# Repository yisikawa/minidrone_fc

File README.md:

# minidrone_fc — ミニドローン制御基板 KiCadプロジェクト

1S LiPo / 8520コアレスモーター×4 / 目標58g・上限70g

回路図は生成済みです。手で描く必要はありません。

---

## 1. 使い方

1. このフォルダごと `D:\KicadProjects\` などに置く（`D:\Kicad`
   の中には置かないでください。KiCad更新時に消える可能性があります）
2. `minidrone_fc.kicad_pro` をダブルクリック
3. 回路図（`.kicad_sch`）を開く

**KiCad 10で開くとファイル形式の変換確認が出ます。**
このプロジェクトはKiCad 7形式で生成されているためです。
「はい」で変換してください。以後は10形式で保存されます。

---

## 2. 最初にやること: XIAOのフットプリント設定

**U1のフットプリントは意図的に空欄にしてあります。**
XIAOはKiCad公式ライブラリに含まれず、環境によってライブラリ名が
変わるため、こちらで決め打ちできませんでした。

手順:

1. https://github.com/Seeed-Studio/OPL_Kicad_Library をZIPで取得
2. 展開し、`Seeed Studio XIAO Series Library/` 内の `.kicad_sym` を
   設定 → シンボルライブラリを管理 から追加
3. フットプリントは `.pretty` フォルダに入っていないと認識されません。
   単体の `.kicad_mod` ファイルの場合は `Seeed_XIAO.pretty` という
   フォルダを作って中に移動してから、
   設定 → フットプリントライブラリを管理 で追加
4. 回路図でU1を選択 → E キー → Footprintフィールドに
   `Seeed_XIAO:XIAO-ESP32C3-SMD` のような実際の名前を入力

U1のシンボル自体はこのプロジェクト内の `minidrone.kicad_sym` に
同梱してあるので、シンボルライブラリの導入は必須ではありません。
必要なのはフットプリントだけです。

---

## 3. 検証済みの内容

このプロジェクトは生成後、KiCadのエンジン（kicad-cli）で
以下を実機検証しています。

| 検証項目 | 結果 |
|---|---|
| 回路図ファイルの読み込み | 成功 |
| 基板ファイルの読み込み | 成功 |
| 部品点数 | 37点（設計意図と一致） |
| フットプリント割り当て | 全点一致（U1除く） |
| ネット数 | 22ネット |
| 接続点の総数 | 96点 |
| ネットリスト照合 | **全ネット完全一致** |
| 意図しない結線 | なし |
| 未結線ピン | 16点（すべてno_connect指定済み） |

つまり、書き出したネットリストが設計表と1本残らず一致することを
確認済みです。回路図の入力ミスはありません。

---

## 4. 設計資料からの変更点

基板化の過程で判明した誤りを訂正しています。

| 項目 | 変更前 | 変更後 | 理由 |
|---|---|---|---|
| 極性コンデンサ | `Device:CP` | `Device:C_Polarized` | CPはKiCad 5時代の名前。現行ライブラリに存在しない |
| フライバックダイオード | SS14 | **SS24** | SS14は1A定格。モーター電流1.62Aに対し余裕が乏しい。SS24は2A定格で、フットプリントは同じD_SMAなのでレイアウト変更不要 |
| C3〜C6の接続先 | Qのドレイン–ソース間 | **VBAT–GND間** | 高周波電流ループを閉じるのは電源側。低側スイッチではこちらが標準 |
| PTCヒューズ・電源SW | あり | **削除** | 6.5Aでは直列抵抗による電圧降下が推力損失に直結する |

---

## 5. ピン割り当て（ESP32-C3の制約を反映済み）

| XIAOピン | GPIO | ネット | 備考 |
|---|---|---|---|
| D0 | GPIO2 | 未使用 | ストラッピングピン。使用不可 |
| D1 | GPIO3 | BATT_SENSE | ADC1。Wi-Fi動作中も使える |
| D2 | GPIO4 | GATE_FL | |
| D3 | GPIO5 | GATE_FR | |
| D4 | GPIO6 | SDA | |
| D5 | GPIO7 | SCL | |
| D6 | GPIO21 | GATE_RL | |
| D7 | GPIO20 | IMU_INT | MPU6050のデータレディ割り込み |
| D8 | GPIO8 | 未使用 | ストラッピングピン |
| D9 | GPIO9 | 未使用 | BOOTピン |
| D10 | GPIO10 | GATE_RR | |

**A0はD0と同一ピンです。** そしてGPIO2はストラッピングピンなので、
電圧センスはD1（GPIO3）に置いてあります。またESP32-C3のADC2は
Wi-Fi動作中に使えないため、ADC1に属するピンでなければなりません。

D7をIMU割り込みに使っているので、将来UART受信機を追加する場合は
再割り当てが必要です。

---

## 6. 次の手順（基板レイアウト）

1. Eeschemaで ツール → フットプリントを割り当て を開き、U1だけ設定
2. 検査 → エレクトリカルルールチェック(ERC) を実行
3. ツール → 基板エディタで基板を更新
4. 基板の外形（Edge.Cuts）を35×35mmで描く
5. 配置は以下の順序で。**この順序が重要です**
   - モーターパッド J2〜J5 を四隅に
   - Q1〜Q4 と D1〜D4 を対応するパッドの直近（5mm以内）に
   - C3〜C6 を各Qの直近に
   - U1を中央、USB-Cが基板端から出る向きに
   - U2を裏面中央、モーター電流経路を避けた位置に
6. デザインルール: 最小クリアランス0.2mm、最小トレース幅0.25mm、
   ビア0.6mm/ドリル0.3mm
7. VBATとGNDはトレースではなく**ベタ（カッパープアー）**で。
   6.5Aには1oz銅で約4.0mm幅のトレースが必要で、35mm角では引けません
8. M_FL〜M_RRは1.0mm幅以上

### レイアウトで最も重要な点

**フライバックループの面積を最小化してください。**
モーターOFFの瞬間、逆起電力が モーター → D → VBAT → モーター を
流れます。このループが囲む面積がそのままノイズの放射源になり、
MPU6050の読み値を汚します。D1〜D4は必ずモーターパッドの真横に、
ビアを挟まずに配置してください。

---

## 7. 未検証事項

- **XIAOフットプリントの実寸**: Seeedのライブラリで裏面パッドや
  サーマルパッドの欠落が報告されています。実物を基板に当てて
  確認してください
- **MPU6050のQFN-24実装**: 手はんだは難度が高めです。困難なら
  GY-521完成基板（+1〜2g）に戻す判断もあり得ます
- **フレーム側の穴位置**: モーターパッドの座標はフレーム設計と
  同時に決める必要があります。基板レイアウトの前にフレーム寸法を
  確定させてください
- **ガーバー出力は未実施**: 発注前にDRCとガーバービューアでの
  目視確認を必ず行ってください

---

## 8. rev2 での修正（ERC結果を反映）

初版に対してERCを実行した結果、エラー3件・警告137件を修正しました。

| 症状 | 件数 | 原因 | 対応 |
|---|---|---|---|
| `power_pin_not_driven` | 3（エラー） | XIAOの3V3ピンを`power_in`と定義していた。実際はレギュレータ**出力**。またGND/VMCUに駆動源が明示されていなかった | 3V3を`power_out`に修正。VBAT/GND/VMCUにPWR_FLAGを追加 |
| `endpoint_off_grid` | 133（警告） | 部品座標が1.27mm（50mil）グリッドに乗っていなかった | 全部品を1.27mmグリッドにスナップ |
| `lib_symbol_mismatch` | 4（警告） | AO3400Aは本来`extends BSS138`の派生シンボル。展開して埋め込んだためライブラリ本体と差異が出る | 下記参照 |

### lib_symbol_mismatch について

これは**動作に影響しない表示上の警告**です。KiCad 7の回路図フォーマットが
`extends` を受け付けないため、生成側で展開する必要がありました。

解消したい場合は、KiCad 10で
**ツール → シンボルをライブラリから更新** を実行してください。
埋め込みコピーがKiCad 10のライブラリ版に置き換わり、警告が消えます。
接続には影響しません。

### 修正後の検証結果

- 回路図・基板ファイルの読み込み: 成功
- ネットリスト照合: **全22ネット・96接続点が完全一致**
- ワイヤ端点198点・ラベル99点・no_connect16点: **すべてグリッド上（off-grid 0）**
- BOM部品数: 37点（PWR_FLAG 3点はBOM除外）

---

## 9. rev2.1 での変更（2026-09-19）: 昇降圧DC-DC追加 + 4層化

### 9.1 なぜ必要だったか — 電源の設計欠陥

改訂前の電源経路は次のとおりでした。

```
VBAT (3.0-4.2V) --[D5 SS24, 約0.4V drop]--> VMCU --> U1(XIAO) pin14 "5V"
                        XIAO内蔵LDO --> +3V3 --> U2 GY-521, U3 BMP280
```

**この基板には昇圧素子が1つもありません。** そのため電池電圧が
「3.3V + LDOドロップアウト」を下回れば、3V3 レールは必ず追従して下がります。

8520コアレスモーター4個で 6.5A を引くと電池は 3.7V→3.4V 程度に沈み、
そこから D5 の 0.4V を引いて VMCU ≈ 3.0V、さらに XIAO 内蔵 LDO の
ドロップアウトを引くと **3V3 は 2.8〜2.95V**。
ESP32-C3 の動作下限 3.0V を公称電圧ですら下回っており、
**スロットルを上げた瞬間に MCU がリセットする**状態でした。

D5 が 0.4V を捨てていたのが最大の要因です。

### 9.2 対策 — TPS63002 昇降圧DC-DC の挿入

```
VBAT --> U4 TPS63002 (昇降圧, 5V固定) --> [D5 SS24] --> VMCU --> XIAO 5Vピン
             |                                              XIAO内蔵LDO --> +3V3（変更なし）
             +-- L1 2.2uH, C10 10uF(in), C11 22uF(out), C12 0.1uF(VINA)
```

- 電池が 3.0V まで落ちても出力5V固定。D5 で 0.4V 落ちても **4.6V** が XIAO に入る。
  内蔵LDO が 3.3V を作るのに必要なのは 3.5V 程度なので**余裕1V以上**
- 3.3V を XIAO の 3V3 ピンに逆流注入せず、XIAO が本来想定する "5V" ピンから
  入れているので、内蔵LDO と競合しない
- **+3V3 ネット（GY-521・BMP280）は一切変更していません**
- D5 は流用。向きも不変で、上流が VBAT から V5V に変わっただけ
- 効率は昇圧90%×LDO66%＝約60%だが、MCU消費0.33Wに対しモーターが24Wなので
  損失増は全体の0.75%

### 9.3 4層化

| 層 | 内容 |
|---|---|
| L1 F.Cu | 信号 + U1/U2 + 既存の VBAT ベタ4枚（そのまま残置） |
| **L2 In1.Cu** | **ベタGND 全面 2949mm²** |
| **L3 In2.Cu** | **VBAT プレーン 全面 2811mm²** |
| L4 B.Cu | 信号 + SMD部品 + GNDベタ |

改訂前は 6.5A を 0.6mm トレースで流していました。内層プレーン全面に変更。
GND スティッチングビアを 133本、衝突判定付きで自動配置しています。

### 9.4 U4 のローカルクリアランス 0.1mm について

VSON-10 は 0.5mm ピッチ・パッド幅 0.28mm でパッド間が 0.22mm しかなく、
VBAT が属する Power ネットクラスの 0.25mm 要求を物理的に満たせません。
Power の 0.25mm はモーター大電流の配線・ベタ向けポリシーであり、
ファインピッチ IC のピン間に適用する意図ではないため、
U4 のフットプリントにローカル上書きを設定しています。
JLCPCB の製造限界は 0.1mm なので 0.22mm は十分製造可能です。

### 9.5 検証結果

| 項目 | 改訂前 | 改訂後 |
|---|---|---|
| DRC エラー | 0 | **0** |
| DRC 警告 | 32 | 37（増分5はすべてシルク重なり） |
| 未配線アイテム | 4 | **1**（改善） |
| schematic_parity | 0 | **0**（回路図と基板が完全一致） |
| ERC | warning 5 / error 0 | warning 5 / error 0（同一） |
| 既存部品のパッド-ネット変更 | — | **D5 pad2 の VBAT→V5V のみ** |

検証は `kicad-cli pcb drc` / `kicad-cli sch erc` で実施しています。
**KiCad MCP の `run_drc` は未接続アイテムを検査しないため、
発注前の最終確認は必ず `kicad-cli` か GUI の DRC で行ってください。**

### 9.6 まだ残っている課題

- **未配線1件**: GND ベタの孤立島が1つ残っています（改訂前は4件）。
  電気的な害はありませんが、気になる場合は GUI で該当箇所を確認してください
- **シルク警告 29+3件**: 新規部品 C10/C11/C12 のリファレンス文字が
  隣接銅箔に重なります。この一角は部品とビアで埋まっており逃がす余地が
  ありませんでした。JLCPCB はパッド上のシルクを自動クリップします
- **Gerber / BOM / 実装座標は再出力していません。** 4層基板として
  出力し直す必要があります
- **実機でのブラウンアウト解消は未検証です**

### 9.7 改訂前の状態に戻すには

改訂前 (rev2) の状態は最初のコミットにそのまま記録してあります。
タグ `rev2` / `rev2.1` から参照できます。

```
git show rev2 --stat      改訂前の内容
git diff rev2 rev2.1      今回の改訂差分
```

git 導入前に使っていた手動チェックポイント (`*.before-gy521`, `*.before-4layer` など)
とローカルのフルバックアップは、履歴で代替できるため追跡対象外にしています
(`.gitignore` 参照)。

詳細な作業記録は `docs/superpowers/plans/2026-09-19-buckboost-and-4layer.md`。

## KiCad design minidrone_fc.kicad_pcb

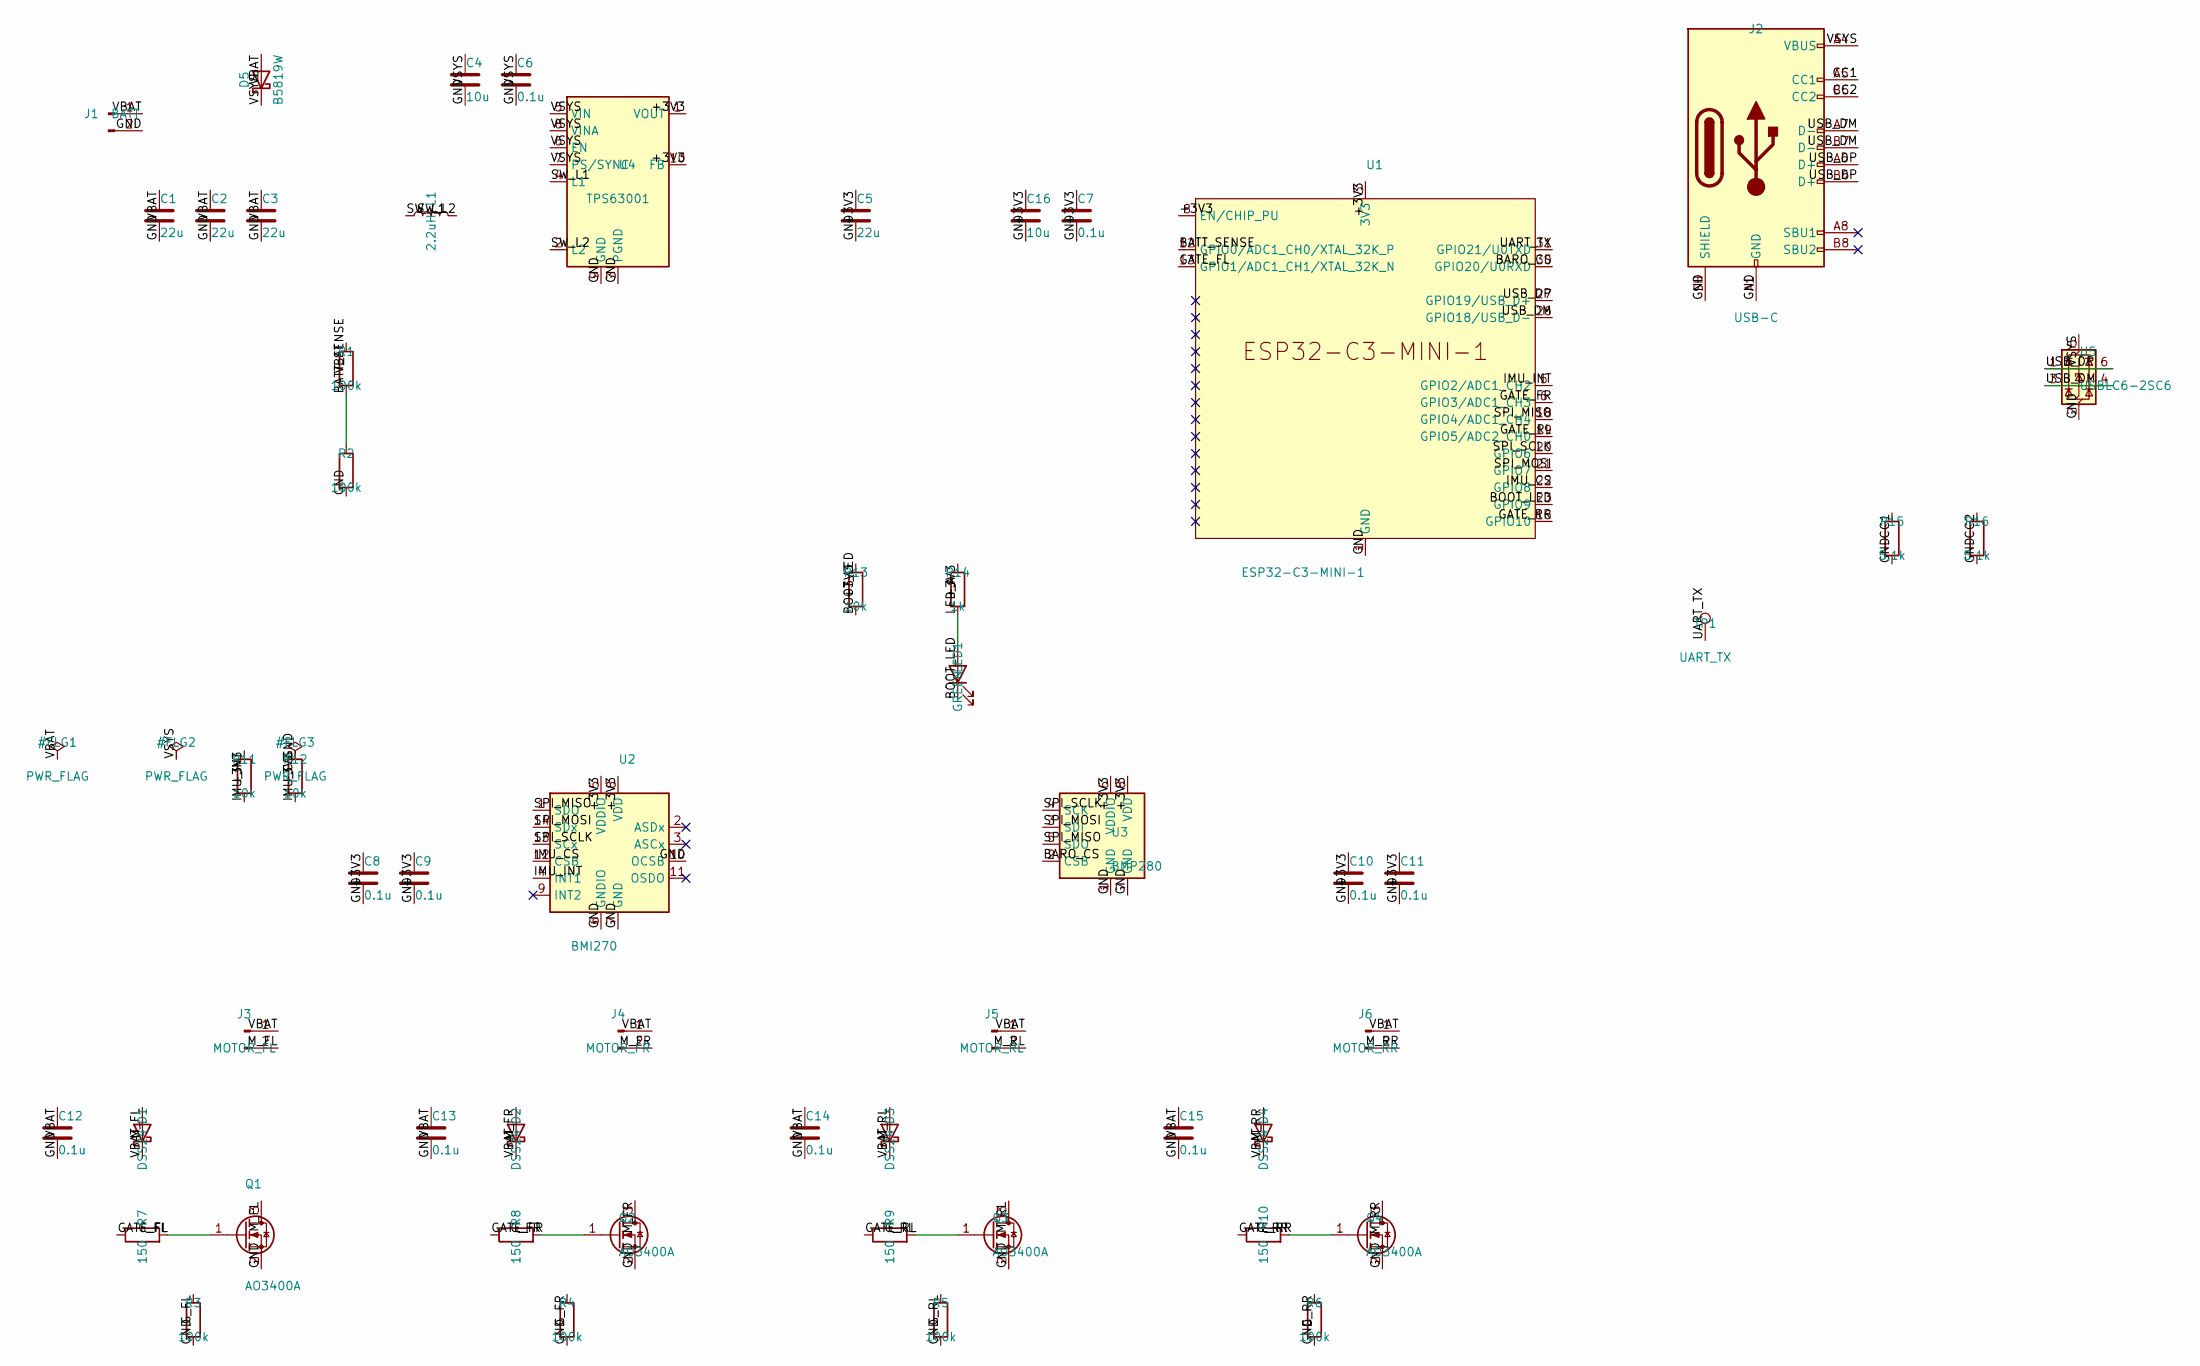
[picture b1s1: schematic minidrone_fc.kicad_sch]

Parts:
C1, C2, C3, C5: 22u; C_0805_2012Metric; LCSC C128856
C4, C16: 10u; C_0805_2012Metric; LCSC C15850
C6, C7, C8, C9, C10, C11, C12, C13, C14, C15: 0.1u; C_0603_1608Metric; LCSC C14663
D1, D2, D3, D4: DSS24; D_SOD-123F; MPN DSS24; LCSC C2923950
D5: B5819W; D_SOD-123; MPN B5819W; LCSC C2943878
J1: BATT; JST_PH_S2B-PH-K_1x02_P2.00mm_Horizontal; MPN S2B-PH-K-S(LF)(SN); LCSC C173752
J2: USB-C; USB_C_Receptacle_HRO_TYPE-C-31-M-12; MPN TYPE-C-31-M-12; LCSC C165948
J3: MOTOR_FL; TestPoint_2Pads_Pitch2.54mm_Drill0.8mm
J4: MOTOR_FR; TestPoint_2Pads_Pitch2.54mm_Drill0.8mm
J5: MOTOR_RL; TestPoint_2Pads_Pitch2.54mm_Drill0.8mm
J6: MOTOR_RR; TestPoint_2Pads_Pitch2.54mm_Drill0.8mm
L1: 2.2uH; L_APV_ANR3015; MPN NRS3015T2R2MNGHV; LCSC C1329483
LED1: GREEN; LED_0603_1608Metric; LCSC C2297
Q1, Q2, Q3, Q4: AO3400A; SOT-23; MPN AO3400A; LCSC C20917
R1, R2, R3, R4, R5, R6: 100k; R_0603_1608Metric; LCSC C25803
R7, R8, R9, R10: 150; R_0603_1608Metric; LCSC C22808
R11, R12, R13: 10k; R_0603_1608Metric; LCSC C130232
R14: 1k; R_0603_1608Metric; LCSC C21190
R15, R16: 5.1k; R_0603_1608Metric; LCSC C23186
TP1: UART_TX; TestPoint_Pad_D1.0mm
U1: ESP32-C3-MINI-1; MPN ESP32-C3-MINI-1-N4; LCSC C2838502
U2: BMI270; Bosch_LGA-14_3x2.5mm_P0.5mm; MPN BMI270; LCSC C2836813
U3: BMP280; Bosch_LGA-8_2x2.5mm_P0.65mm_ClockwisePinNumbering; MPN BMP280; LCSC C22388663
U4: TPS63001; VSON-10-1EP_3x3mm_P0.5mm_EP1.65x2.4mm_ThermalVias; MPN TPS63001DRCR; LCSC C28060
U5: USBLC6-2SC6; SOT-23-6; MPN USBLC6-2SC6; LCSC C2687116

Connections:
+3V3: C5.1, C7.1, C8.1, C9.1, C10.1, C11.1, C16.1, R11.1, R12.1, R13.1, R14.1, U1.3 (3V3), U1.8 (EN/CHIP_PU), U2.5 (VDDIO), U2.8 (VDD), U3.6 (VDDIO), U3.8 (VDD), U4.1 (VOUT), U4.10 (FB)
BARO_CS: U1.30 (GPIO20/U0RXD), U3.2 (CSB)
BATT_SENSE: R1.2, R2.1, U1.12 (GPIO0/ADC1_CH0/XTAL_32K_P)
BOOT_LED: LED1.1 (K), R13.2, U1.23 (GPIO9)
CC1: J2.A5 (CC1), R15.1
CC2: J2.B5 (CC2), R16.1
GATE_FL: R7.1, U1.13 (GPIO1/ADC1_CH1/XTAL_32K_N)
GATE_FR: R8.1, U1.4 (NC), U1.6 (GPIO3/ADC1_CH3)
GATE_RL: R9.1, U1.7 (NC), U1.19 (GPIO5/ADC2_CH0)
GATE_RR: R10.1, U1.16 (GPIO10)
GND: C1.2, C2.2, C3.2, C4.2, C5.2, C6.2, C7.2, C8.2, C9.2, C10.2, C11.2, C12.2, C13.2, C14.2, C15.2, C16.2, J1.2, J2.A1 (GND), J2.A12 (GND), J2.B1 (GND), J2.B12 (GND), J2.SH (SHIELD), Q1.2 (S), Q2.2 (S), Q3.2 (S), Q4.2 (S), R2.2, R3.2, R4.2, R5.2, R6.2, R15.2, R16.2, U1.1 (GND), U1.2 (GND), U1.11 (GND), U1.14 (GND), U1.36 (GND), U1.37 (GND), U1.38 (GND), U1.39 (GND), U1.40 (GND), U1.41 (GND), U1.42 (GND), U1.43 (GND), U1.44 (GND), U1.45 (GND), U1.46 (GND), U1.47 (GND), U1.48 (GND), U1.49 (GND), U1.50 (GND), U1.51 (GND), U1.52 (GND), U1.53 (GND), U2.6 (GNDIO), U2.7 (GND), U2.9 (INT2), U2.10 (OCSB), U2.11 (OSDO), U3.1 (GND), U3.7 (GND), U4.3 (PGND), U4.9 (GND), U4.11 (PGND), U5.2 (GND)
G_FL: Q1.1 (G), R3.1, R7.2
G_FR: Q2.1 (G), R4.1, R8.2
G_RL: Q3.1 (G), R5.1, R9.2
G_RR: Q4.1 (G), R6.1, R10.2
IMU_CS: R12.2, U1.22 (GPIO8), U2.12 (CSB)
IMU_INT: R11.2, U1.5 (GPIO2/ADC1_CH2), U2.4 (INT1)
LED_A: LED1.2 (A), R14.2
M_FL: D1.2 (A), J3.2, Q1.3 (D)
M_FR: D2.2 (A), J4.2, Q2.3 (D)
M_RL: D3.2 (A), J5.2, Q3.3 (D)
M_RR: D4.2 (A), J6.2, Q4.3 (D)
SPI_MISO: U1.18 (GPIO4/ADC1_CH4), U2.1 (SDO), U3.5 (SDO)
SPI_MOSI: U1.21 (GPIO7), U2.14 (SDx), U3.3 (SDI)
SPI_SCLK: U1.20 (GPIO6), U2.13 (SCx), U3.4 (SCK)
SW_L1: L1.1, U4.4 (L1)
SW_L2: L1.2, U4.2 (L2)
UART_TX: TP1.1, U1.31 (GPIO21/U0TXD)
USB_DM: J2.A7 (D-), J2.B7 (D-), U1.26 (GPIO18/USB_D-), U5.3 (I/O2), U5.4 (I/O2)
USB_DP: J2.A6 (D+), J2.B6 (D+), U1.27 (GPIO19/USB_D+), U5.1 (I/O1), U5.6 (I/O1)
VBAT: C1.1, C2.1, C3.1, C12.1, C13.1, C14.1, C15.1, D1.1 (K), D2.1 (K), D3.1 (K), D4.1 (K), D5.2 (A), J1.1, J3.1, J4.1, J5.1, J6.1, R1.1
VSYS: C4.1, C6.1, D5.1 (K), J2.A4 (VBUS), J2.A9 (VBUS), J2.B4 (VBUS), J2.B9 (VBUS), U4.5 (VIN), U4.6 (EN), U4.7 (PS/SYNC), U4.8 (VINA), U5.5 (VBUS)

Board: 4 copper layers, 59 parts (44 on the bottom side), 32 nets, no tracks yet.

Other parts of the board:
MH1, MH2, MH3, MH4: MountingHole_1.5mm
